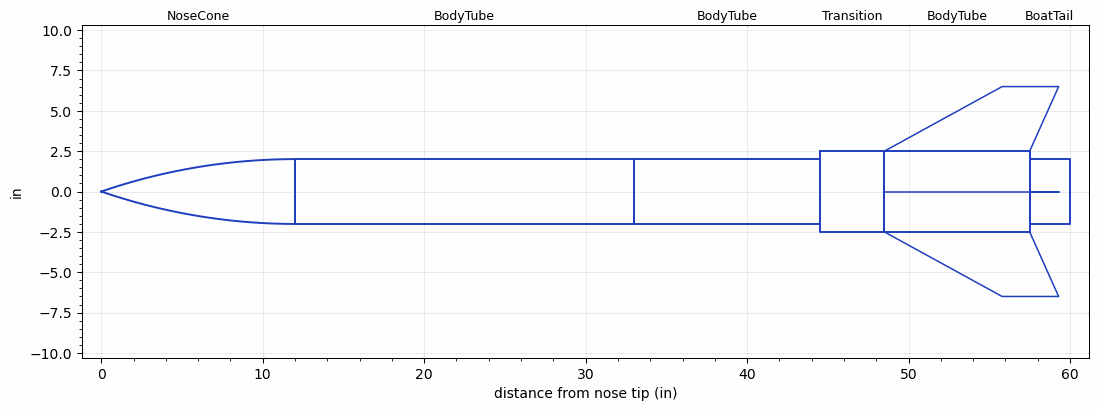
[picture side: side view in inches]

<RASAeroDocument>
 <FileVersion>2</FileVersion>
 <RocketDesign>
  <NoseCone>
   <Length>12</Length>
   <Diameter>4.014</Diameter>
   <Shape>Tangent Ogive</Shape>
   <Location>0</Location>
  </NoseCone>
  <BodyTube>
   <Length>21</Length>
   <Diameter>4.014</Diameter>
   <Location>12</Location>
  </BodyTube>
  <BodyTube>
   <Length>11.5</Length>
   <Diameter>4.014</Diameter>
   <Location>32.9999</Location>
  </BodyTube>
  <Transition>
   <Length>4</Length>
   <Diameter>5</Diameter>
   <RearDiameter>5</RearDiameter>
   <Location>44.4999</Location>
  </Transition>
  <BodyTube>
   <Length>9</Length>
   <Diameter>5</Diameter>
   <Location>48.4999</Location>
   <Fin>
    <Count>4</Count>
    <Chord>9</Chord>
    <Span>4</Span>
    <SweepDistance>7.2948</SweepDistance>
    <TipChord>3.5</TipChord>
    <Thickness>0.118</Thickness>
    <Location>9</Location>
    <AirfoilSection>Rounded</AirfoilSection>
   </Fin>
  </BodyTube>
  <BoatTail>
   <Length>2.5</Length>
   <Diameter>4</Diameter>
   <RearDiameter>4</RearDiameter>
   <Location>57.4999</Location>
  </BoatTail>
  <Surface>Rough Camouflage Paint</Surface>
  <CD>0</CD>
  <ModifiedBarrowman>False</ModifiedBarrowman>
  <Turbulence>False</Turbulence>
  <UseBooster1>False</UseBooster1>
  <UseBooster2>False</UseBooster2>
 </RocketDesign>
 <LaunchSite>
  <Altitude>0</Altitude>
  <Pressure>29.9214</Pressure>
  <RodAngle>0</RodAngle>
  <RodLength>3.2808</RodLength>
  <Temperature>59</Temperature>
  <WindSpeed>4.4739</WindSpeed>
 </LaunchSite>
 <Recovery>
  <Altitude1>1500</Altitude1>
  <Altitude2>656.168</Altitude2>
  <DeviceType1>Parachute</DeviceType1>
  <DeviceType2>Parachute</DeviceType2>
  <Event1>True</Event1>
  <Event2>True</Event2>
  <Size1>71.9999</Size1>
  <Size2>24.9999</Size2>
  <EventType1>Altitude</EventType1>
  <EventType2>Apogee</EventType2>
  <CD1>0.8</CD1>
  <CD2>0</CD2>
 </Recovery>
 <SimulationList>
  <Simulation>
   <SustainerEngine>J525-LW  (LR)</SustainerEngine>
   <SustainerLaunchWt>15.1016</SustainerLaunchWt>
   <SustainerCG>32.9198</SustainerCG>
   <SustainerIgnitionDelay>0</SustainerIgnitionDelay>
   <Booster1SeparationDelay>0</Booster1SeparationDelay>
   <Booster1IgnitionDelay>0</Booster1IgnitionDelay>
   <IncludeBooster1>False</IncludeBooster1>
   <Booster2Delay>0</Booster2Delay>
   <IncludeBooster2>False</IncludeBooster2>
  </Simulation>
  <Simulation>
   <SustainerLaunchWt>14.6889</SustainerLaunchWt>
   <SustainerCG>32.3558</SustainerCG>
   <SustainerIgnitionDelay>0</SustainerIgnitionDelay>
   <Booster1SeparationDelay>0</Booster1SeparationDelay>
   <Booster1IgnitionDelay>0</Booster1IgnitionDelay>
   <IncludeBooster1>False</IncludeBooster1>
   <Booster2Delay>0</Booster2Delay>
   <IncludeBooster2>False</IncludeBooster2>
  </Simulation>
  <Simulation>
   <SustainerLaunchWt>12.3149</SustainerLaunchWt>
   <SustainerCG>28.2753</SustainerCG>
   <SustainerIgnitionDelay>0</SustainerIgnitionDelay>
   <Booster1SeparationDelay>0</Booster1SeparationDelay>
   <Booster1IgnitionDelay>0</Booster1IgnitionDelay>
   <IncludeBooster1>False</IncludeBooster1>
   <Booster2Delay>0</Booster2Delay>
   <IncludeBooster2>False</IncludeBooster2>
  </Simulation>
  <Simulation>
   <SustainerLaunchWt>14.7819</SustainerLaunchWt>
   <SustainerCG>32.5186</SustainerCG>
   <SustainerIgnitionDelay>0</SustainerIgnitionDelay>
   <Booster1SeparationDelay>0</Booster1SeparationDelay>
   <Booster1IgnitionDelay>0</Booster1IgnitionDelay>
   <IncludeBooster1>False</IncludeBooster1>
   <Booster2Delay>0</Booster2Delay>
   <IncludeBooster2>False</IncludeBooster2>
  </Simulation>
  <Simulation>
   <SustainerLaunchWt>17.1519</SustainerLaunchWt>
   <SustainerCG>33.6968</SustainerCG>
   <SustainerIgnitionDelay>0</SustainerIgnitionDelay>
   <Booster1SeparationDelay>0</Booster1SeparationDelay>
   <Booster1IgnitionDelay>0</Booster1IgnitionDelay>
   <IncludeBooster1>False</IncludeBooster1>
   <Booster2Delay>0</Booster2Delay>
   <IncludeBooster2>False</IncludeBooster2>
  </Simulation>
  <Simulation>
   <SustainerLaunchWt>18.0818</SustainerLaunchWt>
   <SustainerCG>36.1959</SustainerCG>
   <SustainerIgnitionDelay>0</SustainerIgnitionDelay>
   <Booster1SeparationDelay>0</Booster1SeparationDelay>
   <Booster1IgnitionDelay>0</Booster1IgnitionDelay>
   <IncludeBooster1>False</IncludeBooster1>
   <Booster2Delay>0</Booster2Delay>
   <IncludeBooster2>False</IncludeBooster2>
  </Simulation>
 </SimulationList>
</RASAeroDocument>
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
